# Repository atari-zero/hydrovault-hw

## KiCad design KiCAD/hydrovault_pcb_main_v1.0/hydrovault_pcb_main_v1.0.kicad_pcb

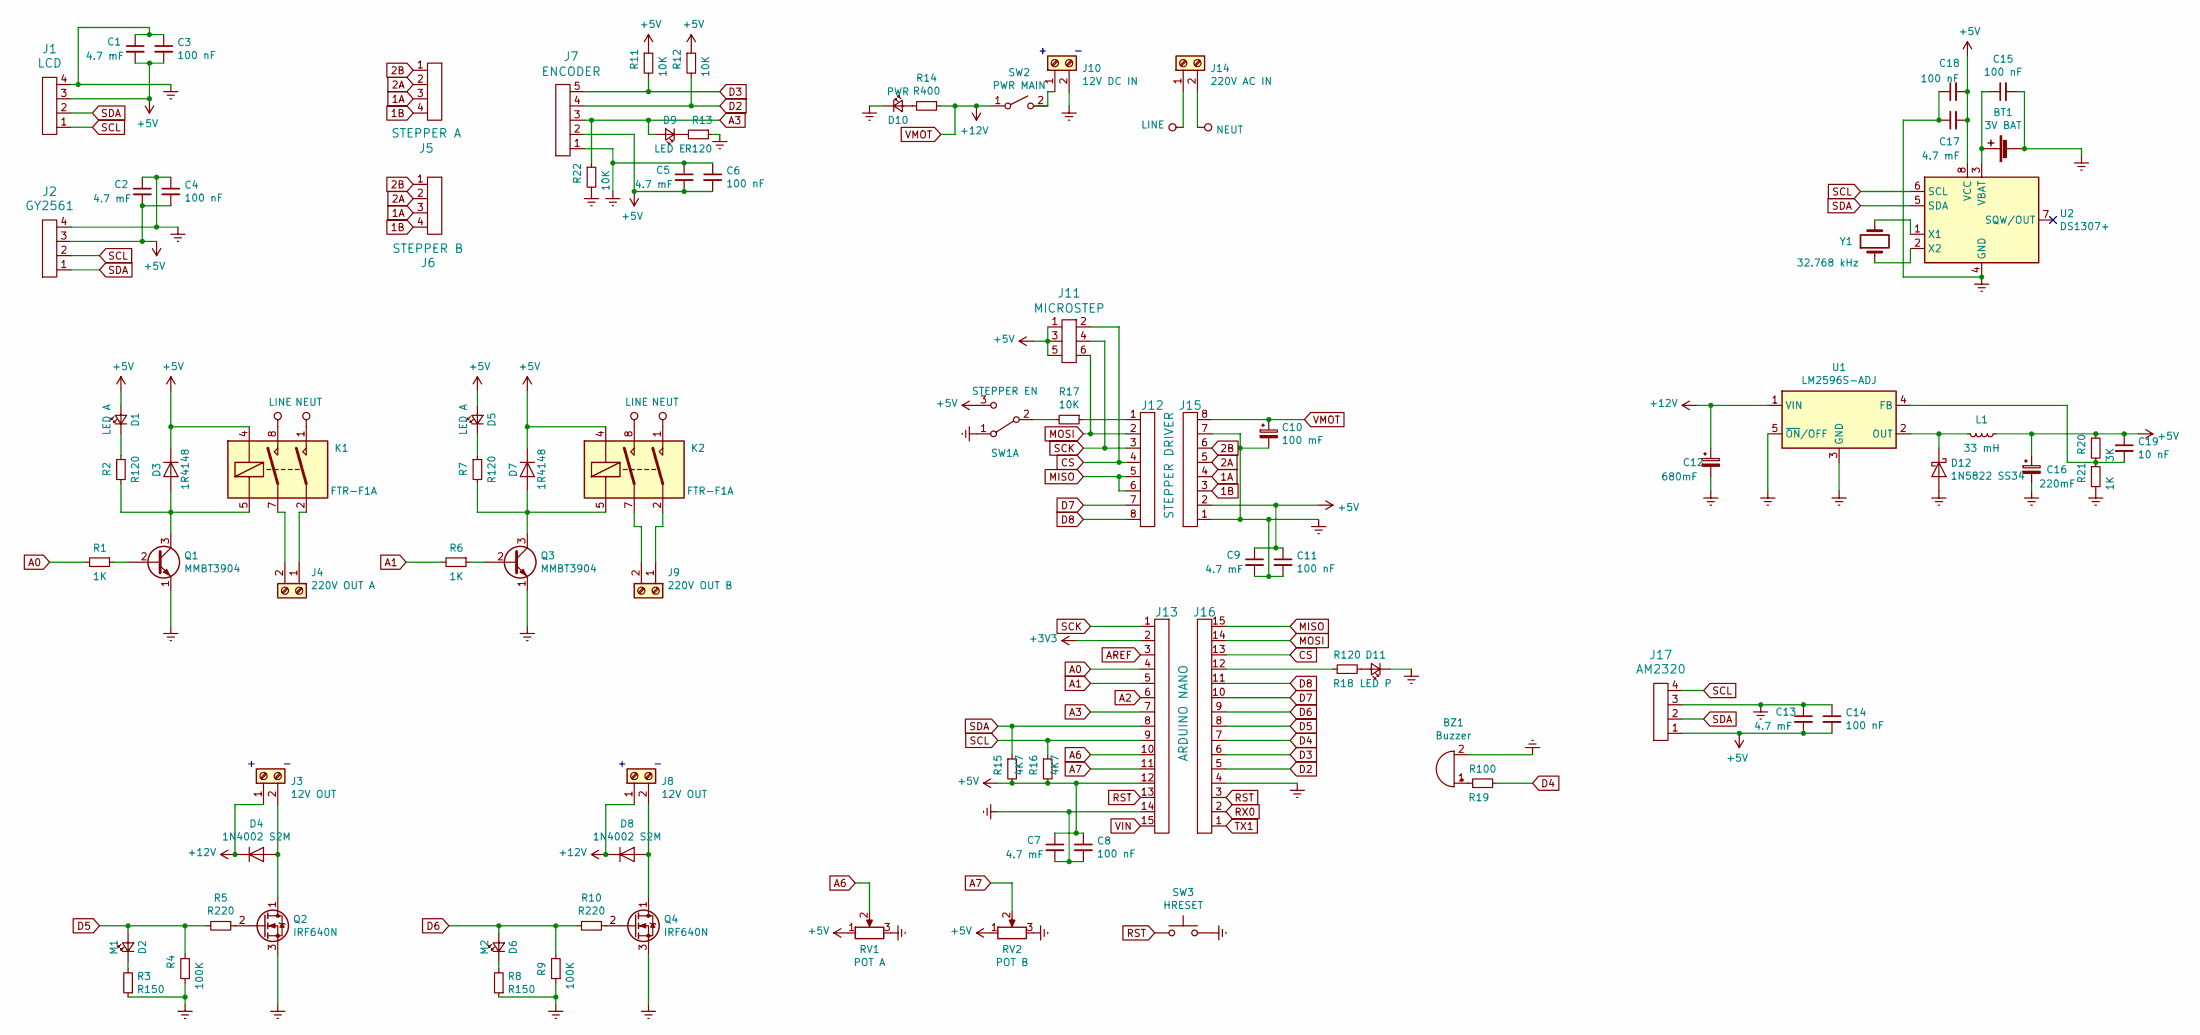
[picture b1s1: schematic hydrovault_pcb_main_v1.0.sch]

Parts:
BT1: 3V BAT; BatteryHolder_ComfortableElectronic_CH273-2450_1x2450
BZ1: Buzzer; Buzzer_12x9.5RM7.6
C1, C2, C5, C7, C9, C13, C17: 4.7 mF; C_1206_3216Metric_Pad1.42x1.75mm_HandSolder
C3, C4, C6, C8, C11, C14, C15, C18: 100 nF; C_1206_3216Metric_Pad1.42x1.75mm_HandSolder
C10: 100 mF; CP_Elec_6.3x7.7
C12: 680mF; CP_Radial_D12.5mm_P5.00mm
C16: 220mF; CP_Elec_10x10
C19: 10 nF; C_1206_3216Metric_Pad1.42x1.75mm_HandSolder
D1, D5: LED A; LED_1206_3216Metric_Pad1.42x1.75mm_HandSolder
D2: M1; LED_1206_3216Metric_Pad1.42x1.75mm_HandSolder
D3, D7: 1R4148; D_SOD-323_HandSoldering
D4, D8: 1N4002 S2M; D_SMA_Handsoldering
D6: M2; LED_1206_3216Metric_Pad1.42x1.75mm_HandSolder
D9: LED E; LED_1206_3216Metric_Pad1.42x1.75mm_HandSolder
D10: PWR; LED_1206_3216Metric_Pad1.42x1.75mm_HandSolder
D11: LED P; LED_1206_3216Metric_Pad1.42x1.75mm_HandSolder
D12: 1N5822 SS34; D_SMC_Handsoldering
J1: LCD; JST_EH_S4B-EH_1x04_P2.50mm_Horizontal
J2: GY2561; JST_EH_S4B-EH_1x04_P2.50mm_Horizontal
J3, J8: 12V OUT; TerminalBlock_Altech_AK300-2_P5.00mm
J4: 220V OUT A; TerminalBlock_Altech_AK300-2_P5.00mm
J5: STEPPER A; JST_EH_S4B-EH_1x04_P2.50mm_Horizontal
J6: STEPPER B; JST_EH_S4B-EH_1x04_P2.50mm_Horizontal
J7: ENCODER; JST_EH_S5B-EH_1x05_P2.50mm_Horizontal
J9: 220V OUT B; TerminalBlock_Altech_AK300-2_P5.00mm
J10: 12V DC IN; TerminalBlock_Altech_AK300-2_P5.00mm
J11: MICROSTEP; PinHeader_2x03_P2.54mm_Vertical
J12, J15: STEPPER DRIVER; PinHeader_1x08_P2.54mm_Vertical
J13, J16: ARDUINO NANO; PinHeader_1x15_P2.54mm_Vertical
J14: 220V AC IN; TerminalBlock_Altech_AK300-2_P5.00mm
J17: AM2320; JST_EH_S4B-EH_1x04_P2.50mm_Horizontal
K1, K2: FTR-F1A; Relay_DPST_Fujitsu_FTR-F1A
L1: 33 mH; L_Bourns_SRP7028A_7.3x6.6mm
Q1, Q3: MMBT3904; SOT-23_Handsoldering
Q2, Q4: IRF640N; ATPAK-2
R1, R6, R21: 1K; R_1206_3216Metric_Pad1.42x1.75mm_HandSolder
R2, R7, R13, R18: R120; R_1206_3216Metric_Pad1.42x1.75mm_HandSolder
R3, R8: R150; R_1206_3216Metric_Pad1.42x1.75mm_HandSolder
R4, R9: 100K; R_1206_3216Metric_Pad1.42x1.75mm_HandSolder
R5, R10: R220; R_1206_3216Metric_Pad1.42x1.75mm_HandSolder
R11, R12, R17, R22: 10K; R_1206_3216Metric_Pad1.42x1.75mm_HandSolder
R14: R400; R_1206_3216Metric_Pad1.42x1.75mm_HandSolder
R15, R16: 4K7; R_1206_3216Metric_Pad1.42x1.75mm_HandSolder
R19: R100; R_1206_3216Metric_Pad1.42x1.75mm_HandSolder
R20: 3K; R_1206_3216Metric_Pad1.42x1.75mm_HandSolder
RV1: POT A; Potentiometer_ACP_CA6-VSMD_Vertical
RV2: POT B; Potentiometer_ACP_CA6-VSMD_Vertical
SW1: STEPPER EN; SW_Slide_1P2T_CK_OS102011MS2Q
SW2: PWR MAIN; SW_Slide_1P2T_CK_OS102011MS2Q
SW3: HRESET; SW_PUSH_6mm
U1: LM2596S-ADJ; TO-263-5_TabPin3
U2: DS1307+; DIP-8_W7.62mm
Y1: 32.768 kHz; Crystal_Round_D2.0mm_Vertical

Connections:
1A: J5.3, J6.3, J15.4
1B: J5.4, J6.4, J15.3
2A: J5.2, J6.2, J15.5
2B: J5.1, J6.1, J15.6
+3V3: J13.2
+5V: C1.2, C2.2, C3.2, C4.2, C5.2, C6.2, C7.1, C8.1, C9.1, C11.1, C13.2, C14.2, C16.1, C17.2, C18.2, C19.1, D1.2 (A), D3.1 (K), D5.2 (A), D7.1 (K), J1.3, J2.3, J7.2, J11.1, J11.3, J11.5, J13.12, J15.2, J17.1, K1.4, K2.4, L1.1, R11.1, R12.1, R15.2, R16.2, R20.1, RV1.1, RV2.1, SW1.3 (C), U2.8 (VCC)
A0: J13.4, R1.2
A1: J13.5, R6.2
A2: J13.6
A3: D9.2 (A), J7.3, J13.7, R22.1
A6: J13.10, RV1.2
A7: J13.11, RV2.2
AREF: J13.3
CS: J11.2, J12.4, J16.13
D2: J7.4, J16.5, R12.2
D3: J7.5, J16.6, R11.2
D4: J16.7, R19.2
D5: D2.2 (A), J16.8, R4.2, R5.2
D6: D6.2 (A), J16.9, R9.2, R10.2
D7: J12.7, J16.10
D8: J12.8, J16.11
Earth: BT1.2 (-), BZ1.2 (+), C1.1, C2.1, C3.1, C4.1, C5.1, C6.1, C7.2, C8.2, C9.2, C10.2, C11.2, C12.2, C13.1, C14.1, C15.2, C16.2, C17.1, C18.1, D10.1 (K), D11.1 (K), D12.2 (A), J1.4, J2.4, J7.1, J10.2, J13.14, J15.1, J15.7, J16.4, J17.3, Q1.1 (E), Q2.3 (S), Q3.1 (E), Q4.3 (S), R3.1, R4.1, R8.1, R9.1, R13.1, R21.2, R22.2, RV1.3, RV2.3, SW1.1 (A), SW3.2, U1.3 (GND), U1.5 (~ON~/OFF), U2.4 (GND)
LINE: J14.1, K1.8, K2.8
MISO: J12.5, J12.6, J16.15
MOSI: J11.6, J12.2, J16.14
NEUT: J14.2, K1.1, K2.1
unnamed: BT1.1 (+), C15.1, U2.3 (VBAT)
unnamed: BZ1.1 (-), R19.1
unnamed: C19.2, R20.2, R21.1, U1.4 (FB)
unnamed: D1.1 (K), R2.1
unnamed: D2.1 (K), R3.2
unnamed: D3.2 (A), K1.5, Q1.3 (C), R2.2
unnamed: D4.2 (A), J3.2, Q2.1 (D)
unnamed: D5.1 (K), R7.1
unnamed: D6.1 (K), R8.2
unnamed: D7.2 (A), K2.5, Q3.3 (C), R7.2
unnamed: D8.2 (A), J8.2, Q4.1 (D)
unnamed: D9.1 (K), R13.2
unnamed: D10.2 (A), R14.2
unnamed: D11.2 (A), R18.2
unnamed: D12.1 (K), L1.2, U1.2 (OUT)
unnamed: J4.1, K1.2
unnamed: J4.2, K1.7
unnamed: J9.1, K2.2
unnamed: J9.2, K2.7
unnamed: J10.1, SW2.2 (B)
unnamed: J12.1, R17.1
unnamed: J16.12, R18.1
unnamed: Q1.2 (B), R1.1
unnamed: Q2.2 (G), R5.1
unnamed: Q3.2 (B), R6.1
unnamed: Q4.2 (G), R10.1
unnamed: R17.2, SW1.2 (B)
unnamed: U2.1 (X1), Y1.2
unnamed: U2.2 (X2), Y1.1
RST: J13.13, J16.3, SW3.1
RX0: J16.2
SCK: J11.4, J12.3, J13.1
SCL: J1.1, J2.2, J13.9, J17.4, R16.1, U2.6 (SCL)
SDA: J1.2, J2.1, J13.8, J17.2, R15.1, U2.5 (SDA)
TX1: J16.1
VIN: J13.15
VMOT: C10.1, C12.1, D4.1 (K), D8.1 (K), J3.1, J8.1, J15.8, R14.1, SW2.1 (A), U1.1 (VIN)

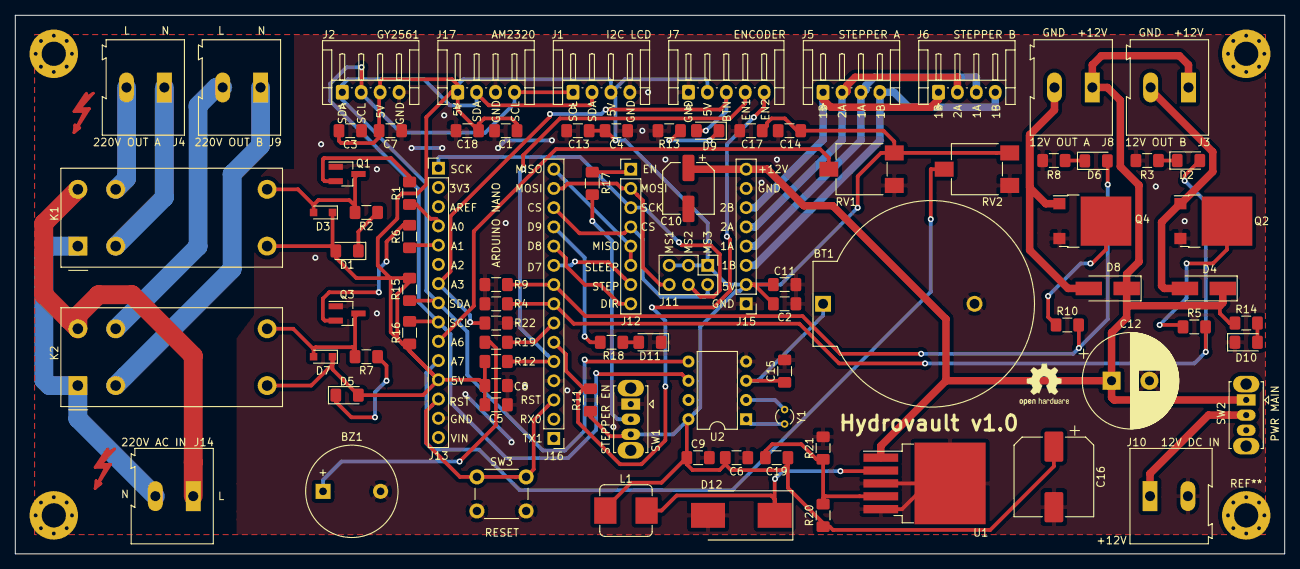
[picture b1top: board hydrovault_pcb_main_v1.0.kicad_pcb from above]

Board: 2 copper layers, 167.6 x 71.1 mm, 87 parts (0 on the bottom side), 57 nets.

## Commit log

2021-08-01 Hydrovault 3D model V1.0
    Fusion 360 model for lasercut, CNC, 3D printing
2021-08-01 PCBs + dxf + images
